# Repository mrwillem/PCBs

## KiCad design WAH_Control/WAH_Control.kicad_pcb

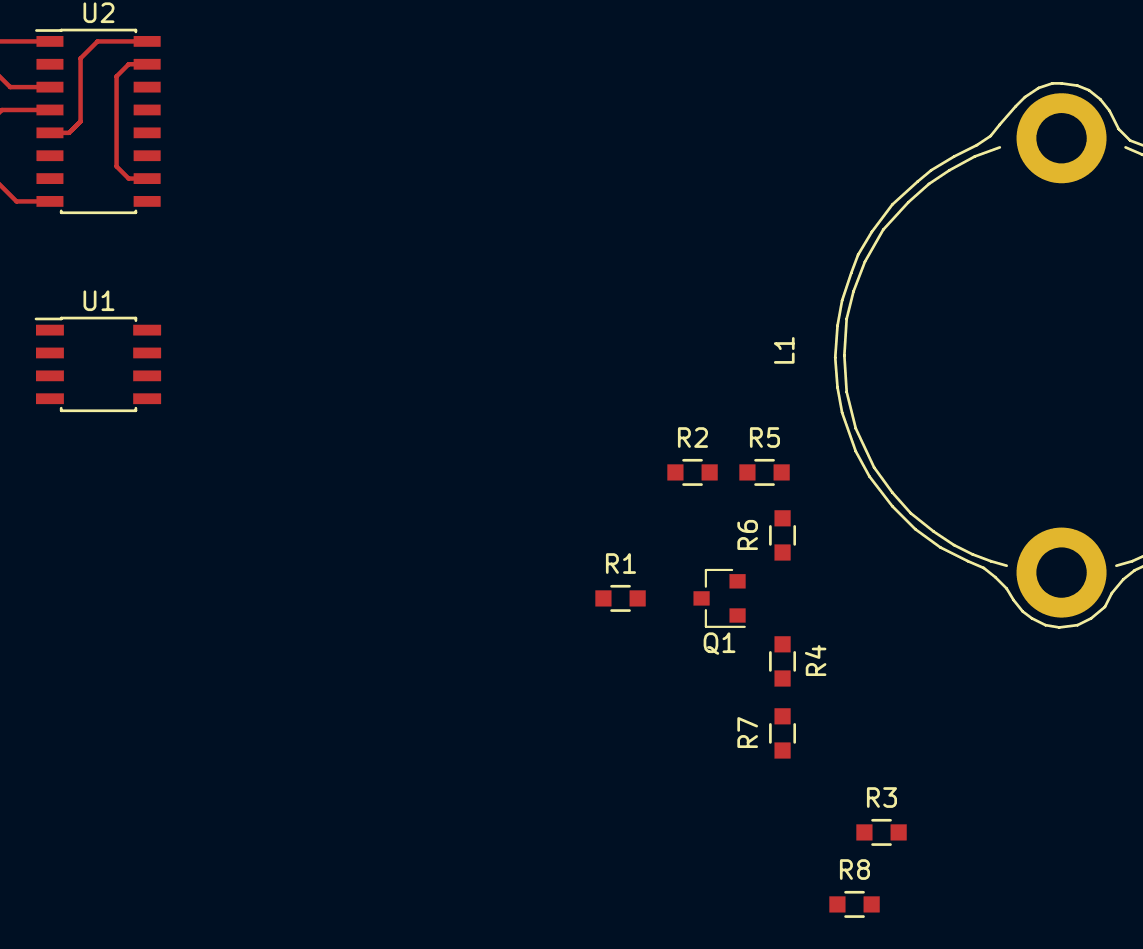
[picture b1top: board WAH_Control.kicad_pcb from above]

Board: 2 copper layers, 12 parts (0 on the bottom side), 10 nets.

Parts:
L1: L; Choke_Radial_27mm_2,8mm-Drills_CD_Bobin_Type_No1410311
Q1: Q_NPN_BEC; SOT-23
R1: 22K; R_0603_HandSolder
R2: 470K; R_0603_HandSolder
R3: 68K; R_0603_HandSolder
R4: 1K5; R_0603_HandSolder
R5: 82K; R_0603_HandSolder
R6: 390R; R_0603_HandSolder
R7, R8: R; R_0603_HandSolder
U1: OPA1642; SOIC-8_3.9x4.9mm_Pitch1.27mm
U2: MAX4622; SOIC-16_3.9x9.9mm_Pitch1.27mm

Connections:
AudioIn: U2.1, U2.3
AudioOut: U2.4, U2.8
FXIN: U2.5, U2.16
GNDA: R5.2, R6.2, U2.6, U2.13
unnamed: Q1.1, R4.1
unnamed: L1.1, R2.2, R5.1
unnamed: L1.2, R4.2, R7.2
unnamed: Q1.2, R6.1
unnamed: Q1.3, R1.2, R2.1
unnamed: U2.10, U2.15
